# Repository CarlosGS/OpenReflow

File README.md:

# OpenReflow
Simple reflow oven controller based on ESP8266

# NOT RECOMMENDED FOR NEW BUILDS!

Please note that for the temperature sensor, I used a voltage divider to read a PT100 element. This makes it necessary to manually calibrate, and even then it wouldn't be as accurate as using a proper RTC reading chip (i.e. MAX31865).

Also the "zero crossing" detector wasn't really necessary for the small wattage and slow pulses involved (at most 1500W at 1Hz). It just adds complexity and makes the board more dangerous by mixing digital and live tracks.

In the end I think it would be more simple to just flash a standard Sonoff switch and wire an external temperature sensor module.

# More information can be found in PCBway

<https://www.pcbway.com/project/shareproject/OpenReflow.html>

# License

Software is GPLv3, Hardware (PCB) is CC-BY-SA.

Author: Carlos Garcia Saura (@CarlosGS)

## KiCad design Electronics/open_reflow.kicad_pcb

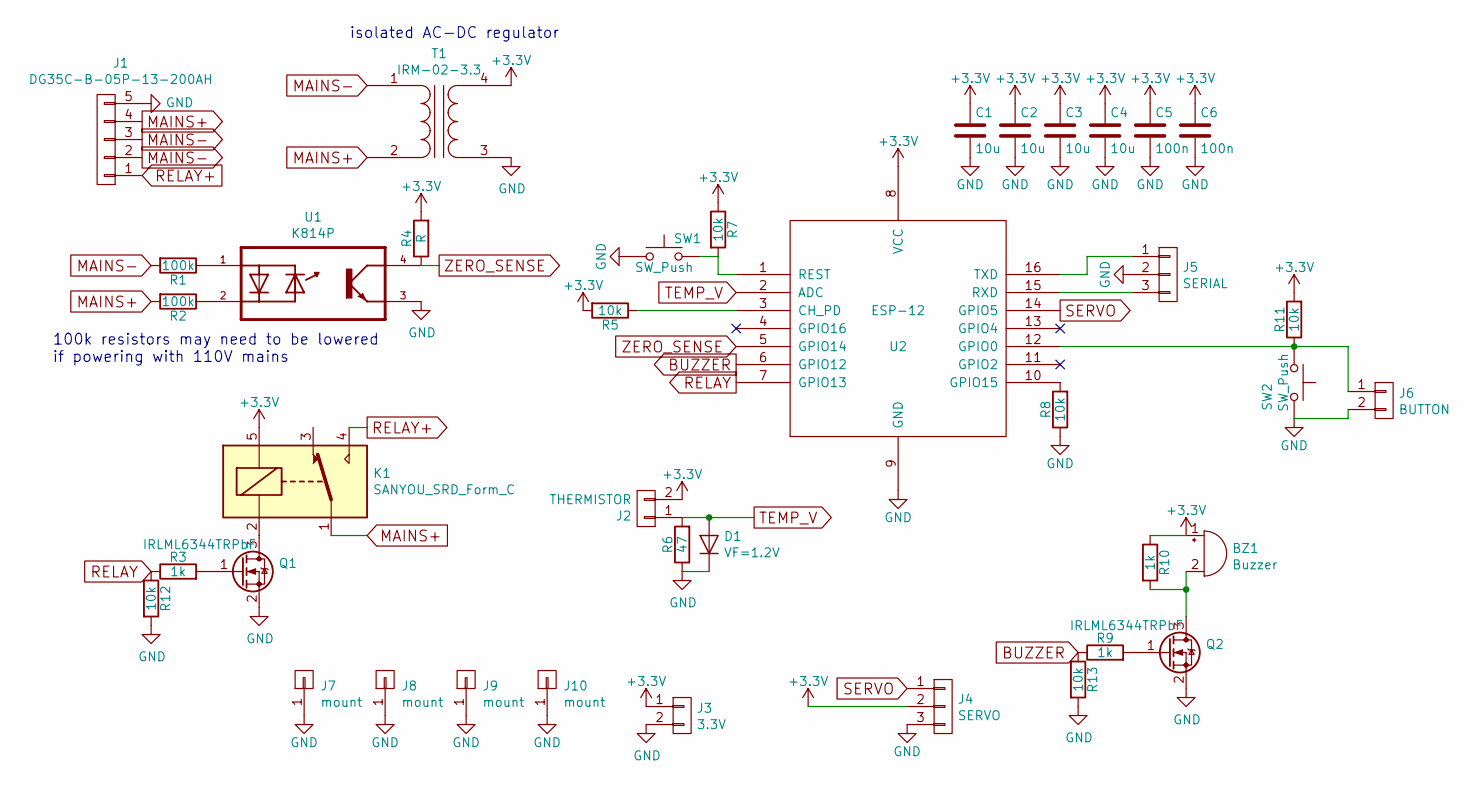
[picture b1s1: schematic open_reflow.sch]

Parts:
BZ1: Buzzer; MagneticBuzzer_ProSignal_ABI-009-RC
C1, C2, C3, C4: 10u; C_1206_HandSoldering
C5, C6: 100n; C_0805_HandSoldering
D1: VF=1.2V; D_SMA
J1: DG35C-B-05P-13-200AH; TerminalBlock_bornier-5_P5.08mm
J2: THERMISTOR; TerminalBlock_bornier-2_P5.08mm
J3: 3.3V; Pin_Header_Straight_1x02_Pitch2.54mm
J4: SERVO; Pin_Header_Straight_1x03_Pitch2.54mm
J5: SERIAL; Pin_Header_Straight_1x03_Pitch2.54mm
J6: BUTTON; Pin_Header_Straight_1x02_Pitch2.54mm
J7, J8, J9, J10: mount; MountingHole_4.5mm_Pad
K1: SANYOU_SRD_Form_C; Relay_SPDT_SANYOU_SRD_Series_Form_C
Q1, Q2: IRLML6344TRPbF; SOT-23
R1, R2: 100k; R_1206_HandSoldering
R3, R9, R10: 1k; R_0805_HandSoldering
R4: R; R_0805_HandSoldering
R5, R7, R8, R11, R12, R13: 10k; R_0805_HandSoldering
R6: 47; R_0805_HandSoldering
SW1, SW2: SW_Push; smd_button
T1: IRM-02-3.3; ACDC-Converter_MeanWell-IRM-02-x
U1: K814P; DIP762W50P254L458H480Q4
U2: ESP-12

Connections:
+3V3: BZ1.1 (-), C1.1, C2.1, C3.1, C4.1, C5.1, C6.1, J2.2, J3.1, J4.2, K1.5, R4.2, R5.2, R7.1, R10.1, R11.2, T1.4 (SB), U2.8 (VCC)
BUZZER: R9.1, R13.1, U2.6 (GPIO12)
GND: C1.2, C2.2, C3.2, C4.2, C5.2, C6.2, D1.1 (K), J1.5, J3.2, J4.3, J5.2, J6.2, J7.1, J8.1, J9.1, J10.1, Q1.2 (S), Q2.2 (S), R6.1, R8.1, R12.2, R13.2, SW1.1, SW2.2, T1.3 (SA), U1.3, U2.9 (GND)
MAINS+: J1.4, K1.1, R2.2, T1.2 (AB)
MAINS-: J1.2, J1.3, R1.2, T1.1 (AA)
unnamed: BZ1.2 (+), Q2.3 (D), R10.2
unnamed: J5.1, U2.16 (TXD)
unnamed: J5.3, U2.15 (RXD)
unnamed: J6.1, R11.1, SW2.1, U2.12 (GPIO0)
unnamed: K1.2, Q1.3 (D)
unnamed: Q1.1 (G), R3.2
unnamed: Q2.1 (G), R9.2
unnamed: R1.1, U1.1
unnamed: R2.1, U1.2
unnamed: R5.1, U2.3 (CH_PD)
unnamed: R7.2, SW1.2, U2.1 (REST)
unnamed: R8.2, U2.10 (GPIO15)
RELAY: R3.1, R12.1, U2.7 (GPIO13)
RELAY+: J1.1, K1.4
SERVO: J4.1, U2.14 (GPIO5)
TEMP_V: D1.2 (A), J2.1, R6.2, U2.2 (ADC)
ZERO_SENSE: R4.1, U1.4, U2.5 (GPIO14)

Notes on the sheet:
100k resistors may need to be lowered if powering with 110V mains
isolated AC-DC regulator

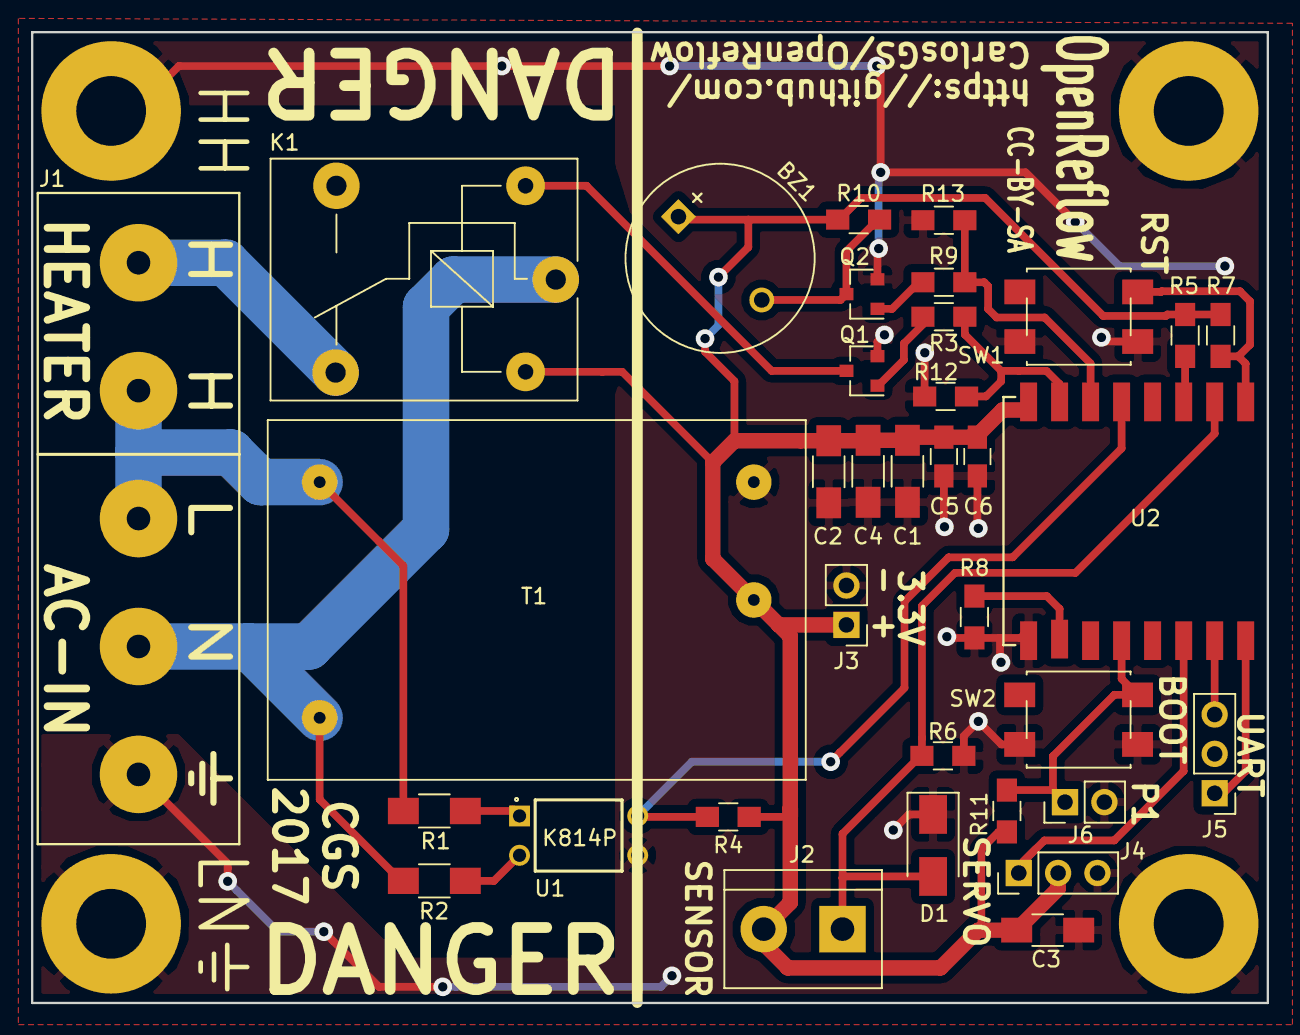
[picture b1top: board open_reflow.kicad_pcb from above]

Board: 2 copper layers, 79.7 x 62.6 mm, 39 parts (0 on the bottom side), 22 nets.

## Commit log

2017-11-10 Added project sources
2017-11-10 Added reflow profile & circuit diagram
2017-11-10 Added PCB picture
